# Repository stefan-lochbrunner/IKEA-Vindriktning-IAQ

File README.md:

# IKEA-Vindriktning-IAQ
IKEA Vindriktning + BME688 + SGP30 + WS2812 connected to an ESP8266 running Tasmota

For more details see project on [Hackaday.io](https://hackaday.io/project/185960-ikea-vindriktning-iaq).

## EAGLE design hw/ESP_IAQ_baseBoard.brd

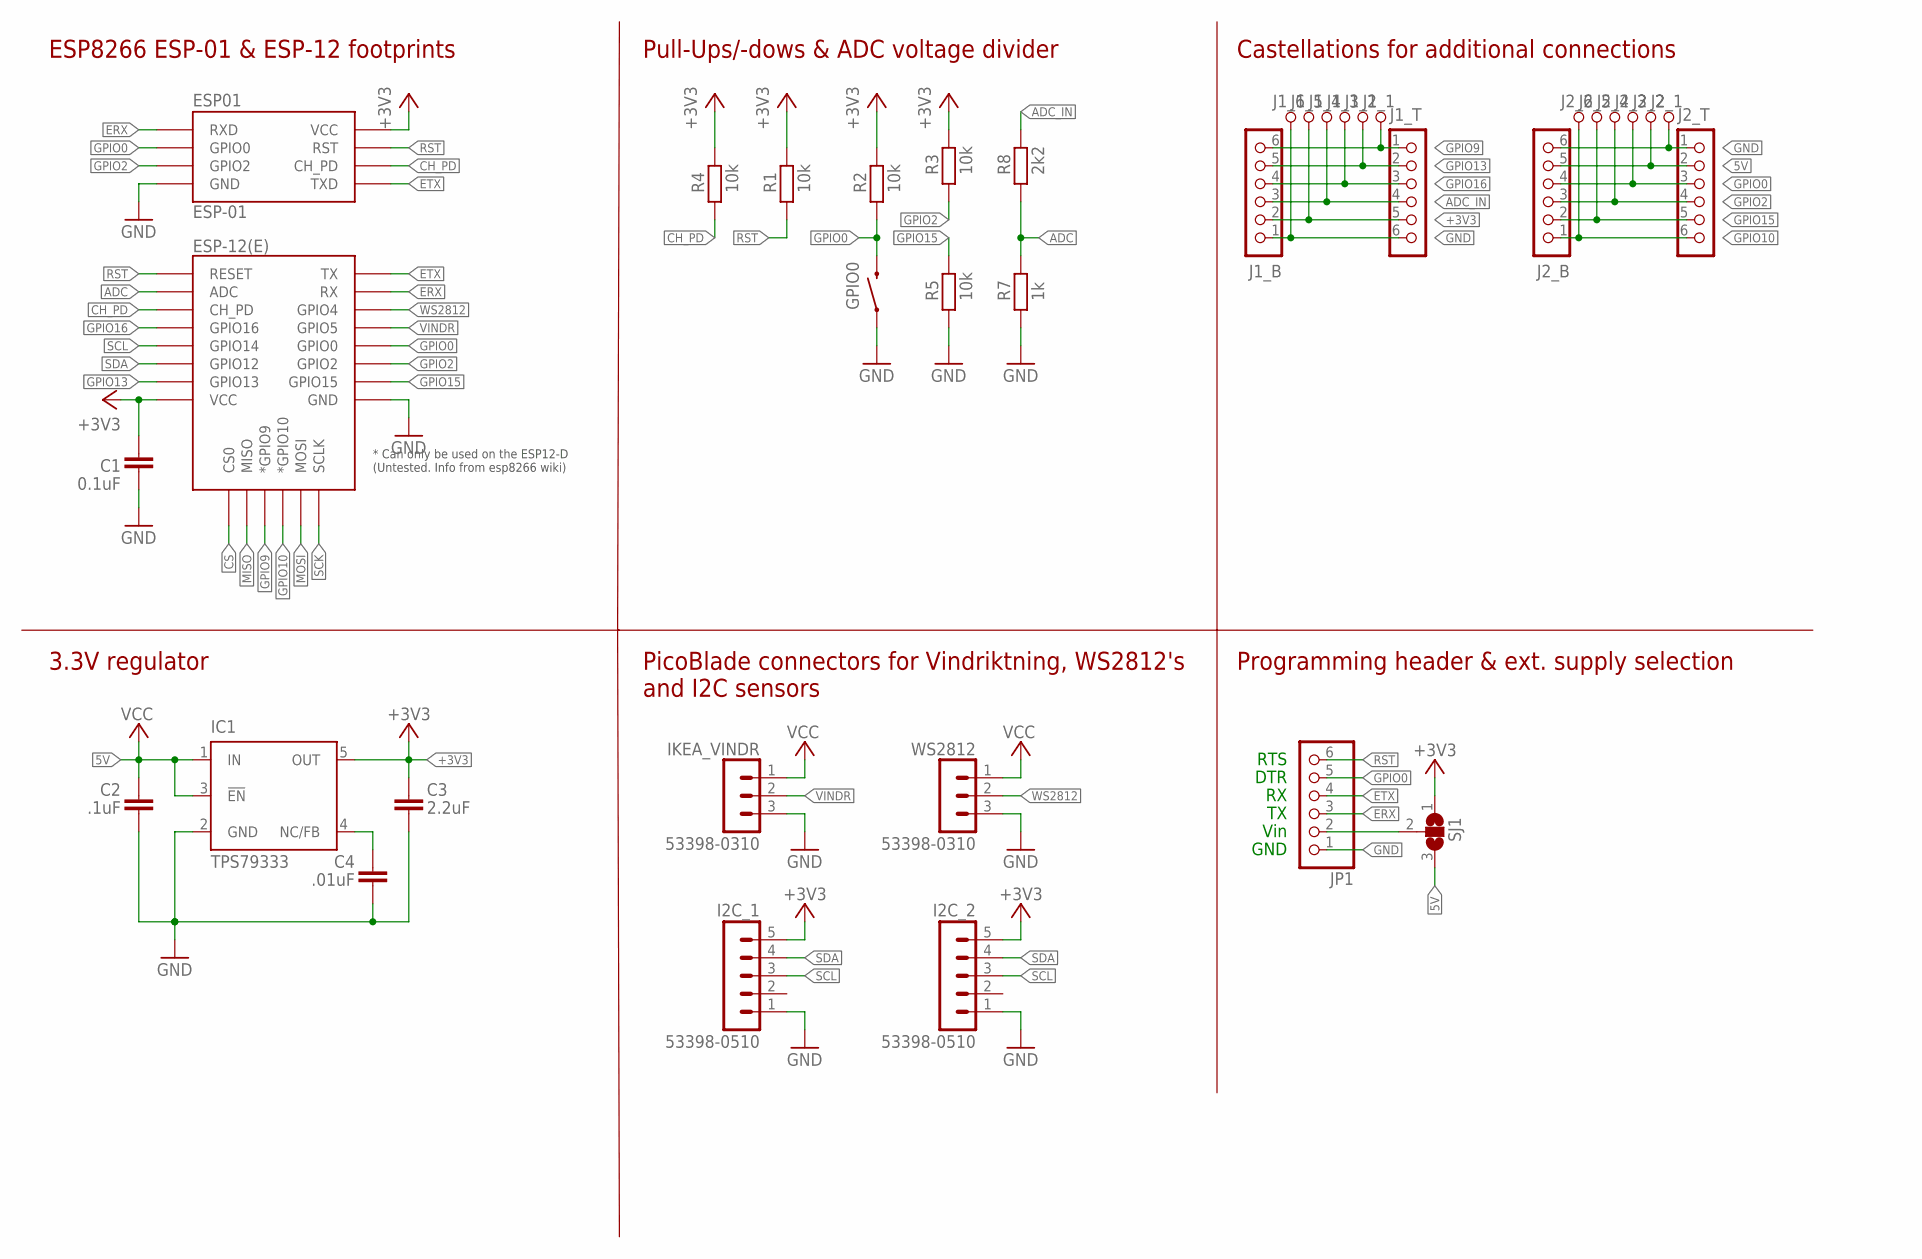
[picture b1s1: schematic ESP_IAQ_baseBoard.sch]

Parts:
C1: 0.1uF; C805
C2: .1uF; C805
C3: 2.2uF; C805
C4: .01uF; C805
ESP-01: ESP01
ESP-12(E): ESP12ESMD; ESP12E-SMD
GPIO0: MOMENTARY-SWITCH-SPST-SMD-RIGHT-ANGLE; TACTILE_SWITCH_SMD_RIGHT_ANGLE
I2C_1, I2C_2: 53398-0510
IC1: TPS79333; SOT23-DBV
IKEA_VINDR: 53398-0310
J1_1, J1_2, J1_3, J1_4, J1_5, J1_6, J2_1, J2_2, J2_3, J2_4, J2_5, J2_6: PAD_TERMINAL-1.02MM_ROUND; CON_PAD_ROUND_1.02MM
J1_B, J1_T, J2_B, J2_T: CON_HEADER_1X06-SMD-RIGHT-ANGLED; M1X6_MALE_RIGHT_ANGLED_SMD
JP1: PINHD-1X6LOCK; 1X06-BIGLOCK
R1, R2, R3, R4, R5: 10k; R603
R7: 1k; R603
R8: 2k2; R603
SJ1: SJ2W; SJ_2
WS2812: 53398-0310

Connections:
5V: C2.1, IC1.1 (IN), IC1.3 (!EN), IKEA_VINDR.1, J2_2.P, J2_B.5, J2_T.2, SJ1.3, WS2812.1
+3V3: C1.1, C3.1, ESP-01.VCC, ESP-12(E).VCC, I2C_1.5, I2C_2.5, IC1.5 (OUT), J1_5.P, J1_B.2, J1_T.5, R1.2, R2.2, R3.2, R4.2, SJ1.1
ADC: ESP-12(E).ADC, R7.2, R8.1
ADC_IN: J1_4.P, J1_B.3, J1_T.4, R8.2
BYPASS: C4.1, IC1.4 (NC/FB)
CH_PD: ESP-01.CH_PD, ESP-12(E).CH_PD, R4.1
CS: ESP-12(E).CS0
ERX: ESP-01.RX (RXD), ESP-12(E).RXD0 (RX), JP1.3
ETX: ESP-01.TX (TXD), ESP-12(E).TXD0 (TX), JP1.4
GND: C1.2, C2.2, C3.2, C4.2, ESP-01.GND, ESP-12(E).GND, GPIO0.1, I2C_1.1, I2C_2.1, IC1.2 (GND), IKEA_VINDR.3, J1_6.P, J1_B.1, J1_T.6, J2_1.P, J2_B.6, J2_T.1, JP1.1, R5.1, R7.1, WS2812.3
GPIO0: ESP-01.GPIO0, ESP-12(E).GPIO0, GPIO0.2, J2_3.P, J2_B.4, J2_T.3, JP1.5, R2.1
GPIO2: ESP-01.GPIO2, ESP-12(E).GPIO2, J2_4.P, J2_B.3, J2_T.4, R3.1
GPIO9: ESP-12(E).GPIO9 (*GPIO9), J1_1.P, J1_B.6, J1_T.1
GPIO10: ESP-12(E).GPIO10 (*GPIO10), J2_6.P, J2_B.1, J2_T.6
GPIO13: ESP-12(E).GPIO13, J1_2.P, J1_B.5, J1_T.2
GPIO15: ESP-12(E).GPIO15, J2_5.P, J2_B.2, J2_T.5, R5.2
GPIO16: ESP-12(E).GPIO16, J1_3.P, J1_B.4, J1_T.3
MISO: ESP-12(E).MISO
MOSI: ESP-12(E).MOSI
RST: ESP-01.RST, ESP-12(E).RESET, JP1.6, R1.1
SCK: ESP-12(E).SCLK
SCL: ESP-12(E).GPIO14, I2C_1.3, I2C_2.3
SDA: ESP-12(E).GPIO12, I2C_1.4, I2C_2.4
VIN: JP1.2, SJ1.2
VINDR: ESP-12(E).GPIO5, IKEA_VINDR.2
WS2812: ESP-12(E).GPIO4, WS2812.2

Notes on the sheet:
DTR
RTS
Vin
GND
ESP8266 ESP-01 & ESP-12 footprints
3.3V regulator
Pull-Ups/-dows & ADC voltage divider
PicoBlade connectors for Vindriktning, WS2812's and I2C sensors
Castellations for additional connections
Programming header & ext. supply selection

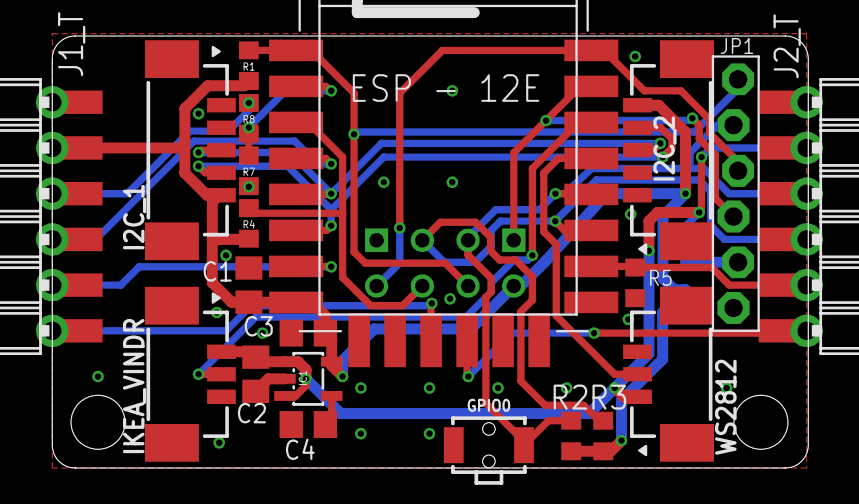
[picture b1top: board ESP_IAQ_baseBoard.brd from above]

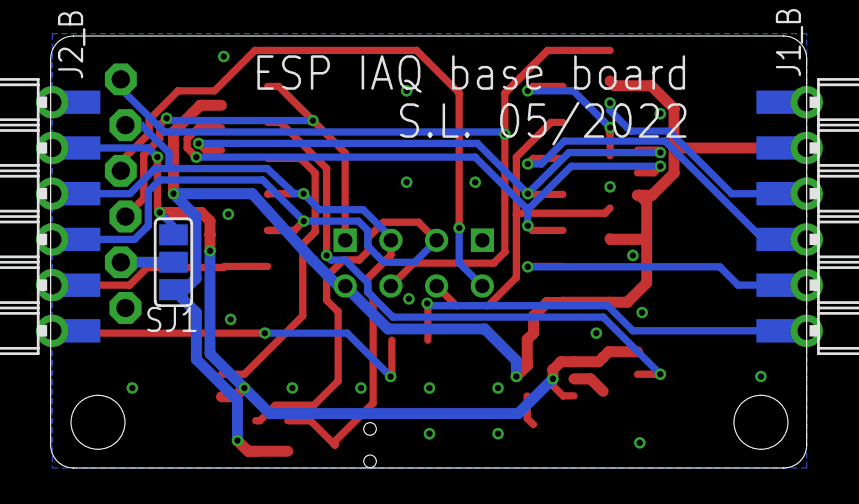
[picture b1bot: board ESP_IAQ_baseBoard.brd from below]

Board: 2 copper layers, 42.0 x 24.0 mm, 37 parts (3 on the bottom side), 22 nets.

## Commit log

2022-11-30 Added Eagle schematic and PCB layout.
2022-11-30 Updated README.md.

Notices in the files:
parts and their libraries:
SparkFun-Switches: Licensing: Creative Commons ShareAlike 4.0 International - https://creativecommons.org/licenses/by-sa/4.0
con-molex-picoblade: Copyright (C) 2010, Bob Starr
